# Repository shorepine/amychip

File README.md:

# AMY on a chip 

This repository collects "AMYchip" implementations, where we run the [AMY](https://github.com/shorepine/AMY) synthesizer on a full chip (doing nothing else), servicing requests over i2c (and future, SPI etc).

We have
 - [`esp32s3`](https://github.com/shorepine/amychip/tree/main/esp32s3)

And soon want to have
 - `rp2350`
 - `esp32p4`
 - `daisy`

## How to

Set your I2S and I2C pins at the top of the `amychip.c` in your chip's folder:

```c
#define I2S_BCLK 13 
#define I2S_LRCLK 12
#define I2S_DIN 11 // data going to the codec, eg DAC data
#define I2C_SLAVE_SCL 5  
#define I2C_SLAVE_SDA 4 
#define I2C_MASTER_SCL 17
#define I2C_MASTER_SDA 18
#define I2S_DOUT 16 // data coming from the codec, eg ADC  data
```

Set up your DAC / ADC codec. I'm using the [`WM8960`](https://www.sparkfun.com/products/21250) codec. Wire it up like:

```
Tulip or etc I2C/Mabee/Grove SCL -> I2C_SLAVE_SCL
Tulip or etc I2C/Mabee/Grove SDA -> I2C_SLAVE_SDA
Tulip or etc I2C/Mabee/Grove GND -> MCU GND
Tulip or etc I2C/Mabee/Grove 3.3V -> MCU 3V3
USB 5V -> MCU (we need 5V to power this codec)
WM8960 GND -> Audio in sleeve/GND
WM8960 LINPUT1 -> Audio in L
WM8960 RINPUT1 -> Audio in R
WM8960 HPL -> Audio out L
WM8960 OUT3 -> Audio out sleeve  *** NOTE: Audio-out "ground" is actually a special "mid-voltage" on OUT3
WM8960 HPR -> Audio out R
WM8960 BLCK -> I2S_BCLK
WM8960 DACLRC -> I2S_LRCLK (shared)
WM8960 DACDAT -> I2S_DIN
WM8960 ADCLRC -> I2S_LRCLK (shared)
WM8960 ADCDAT -> I2S_DOUT
WM8960 SCL -> I2C_MASTER_SCL
WM8960 SDA -> I2C_MASTER_SDA
WM8960 3V3 -> MCU 3V3
WM8960 VIN -> MCU 5V 
WM8960 GND -> MCU GND 
```

Compile / flash `amychip` using the instructions in the chip's folder.

Control the chip over I2C. In e.g. Tulip, that's as simple as 

```python
from machine import I2C
import amy
i2c = I2C(0, freq=400000)

amy.override_send= lambda x : i2c.writeto(0x58, bytes(x.encode('ascii')))
amy.send(reset=amy.RESET_TIMEBASE, time=tulip.ticks_ms()) # Restart the clock
```

You can get this on Tulip World:

```python
world.download('amychip.py')
execfile('amychip.py')
```

## Protocol

For now, over i2c, we just send AMY messages encoded as ASCII to `0x58`. Nothing gets returned. 

TODO:
 - ~~`memorypcm` / sample loading~~
 - stderr feedback over I2C
 - `sequencer.c`, sending interrupts to the "main" i2c host
 - SPI? UART?

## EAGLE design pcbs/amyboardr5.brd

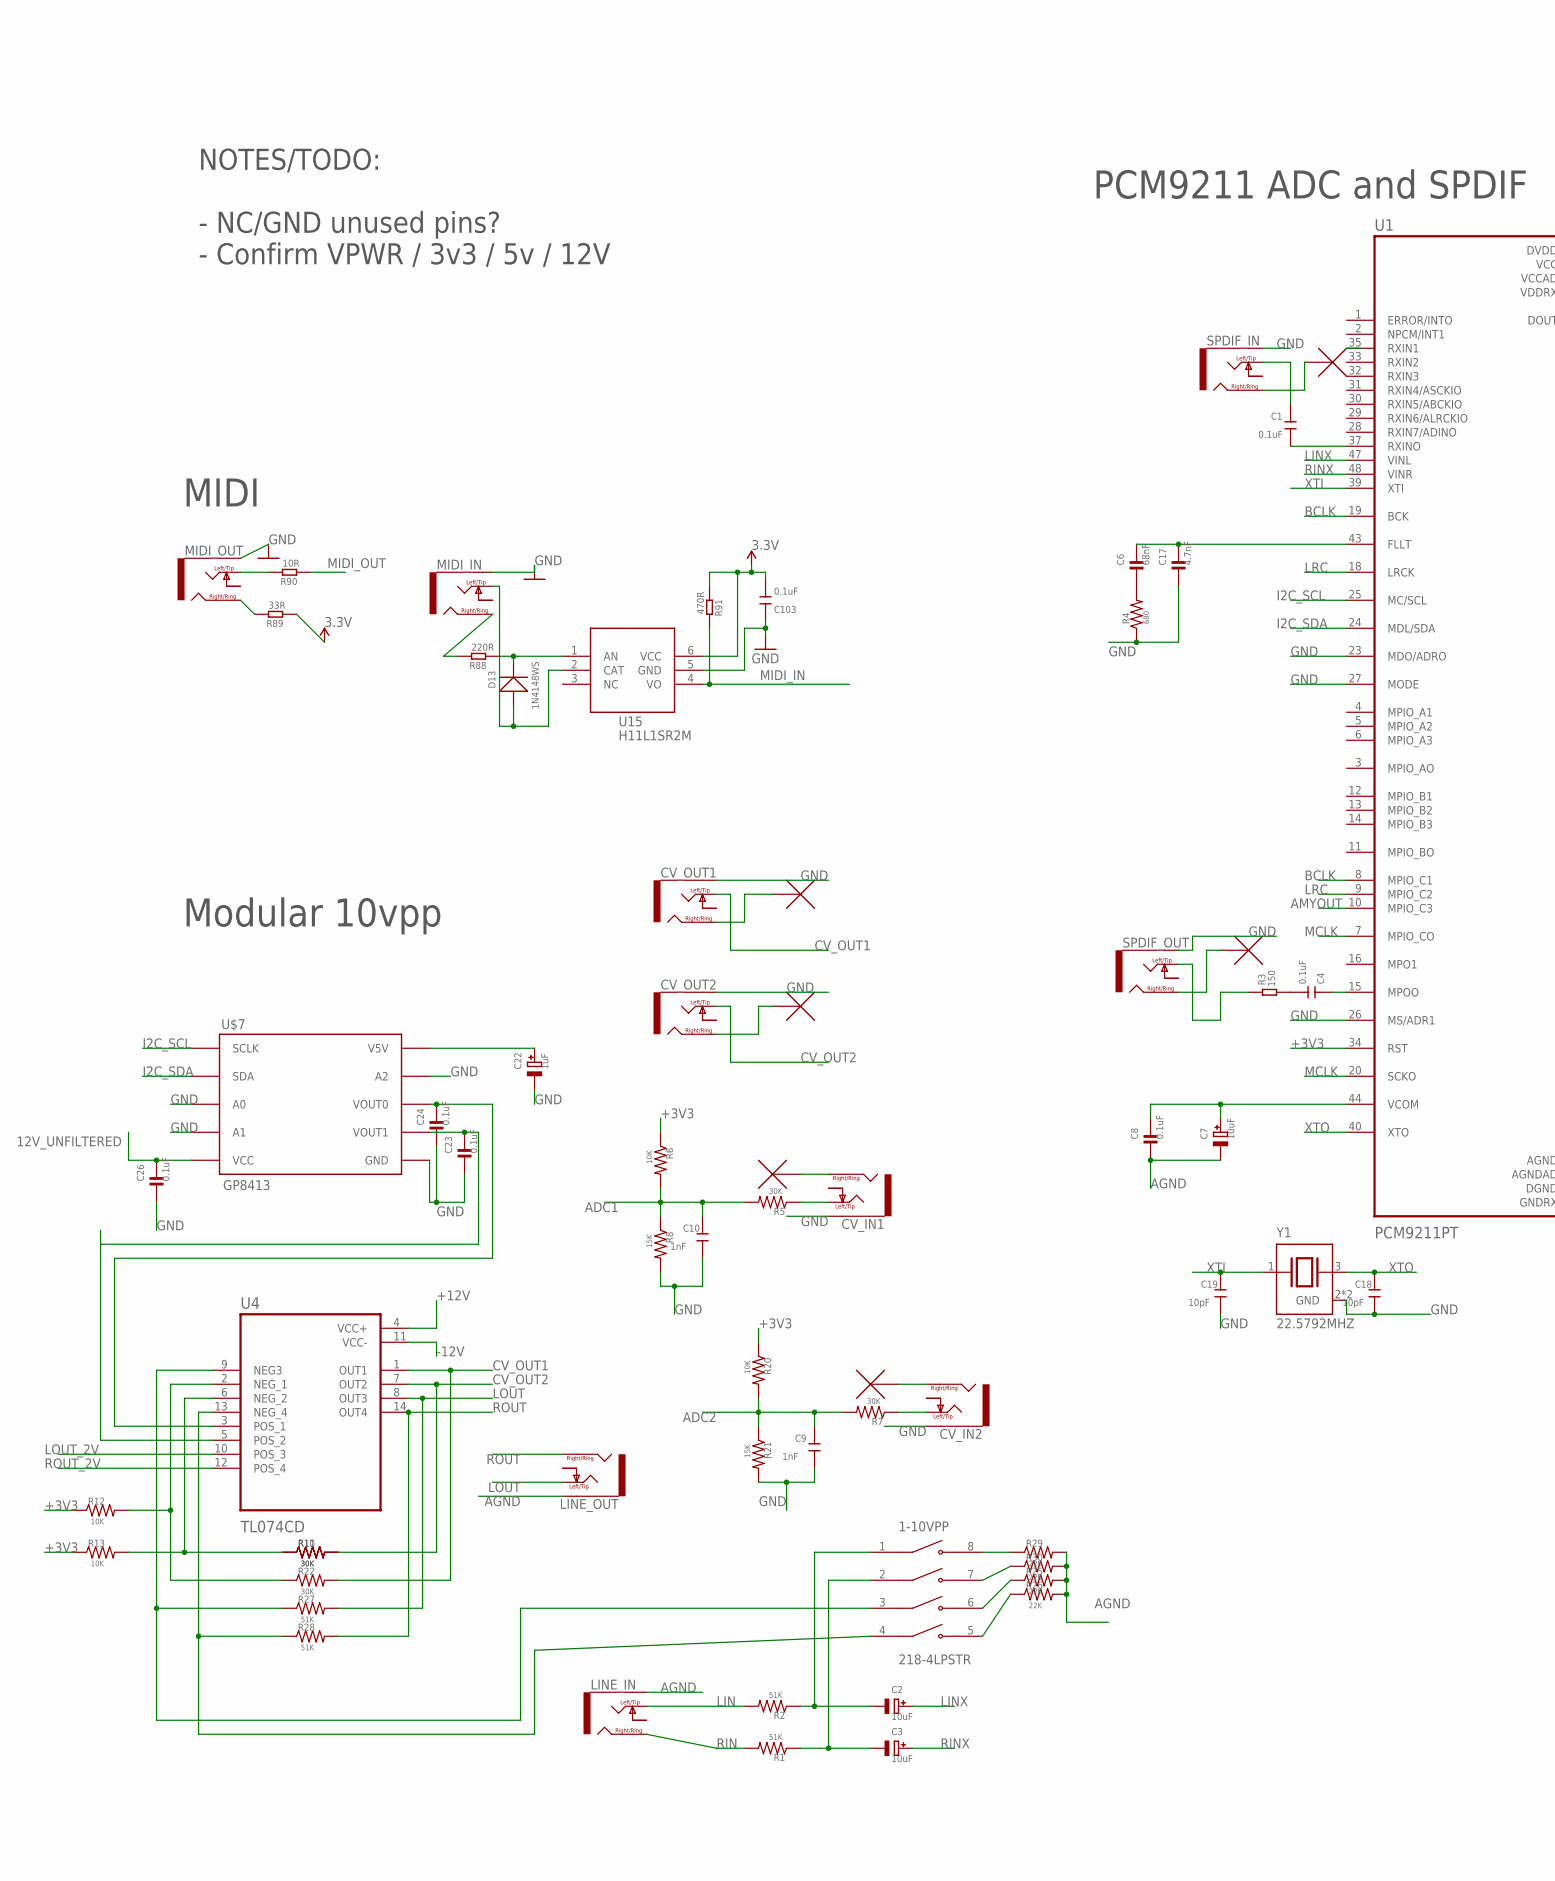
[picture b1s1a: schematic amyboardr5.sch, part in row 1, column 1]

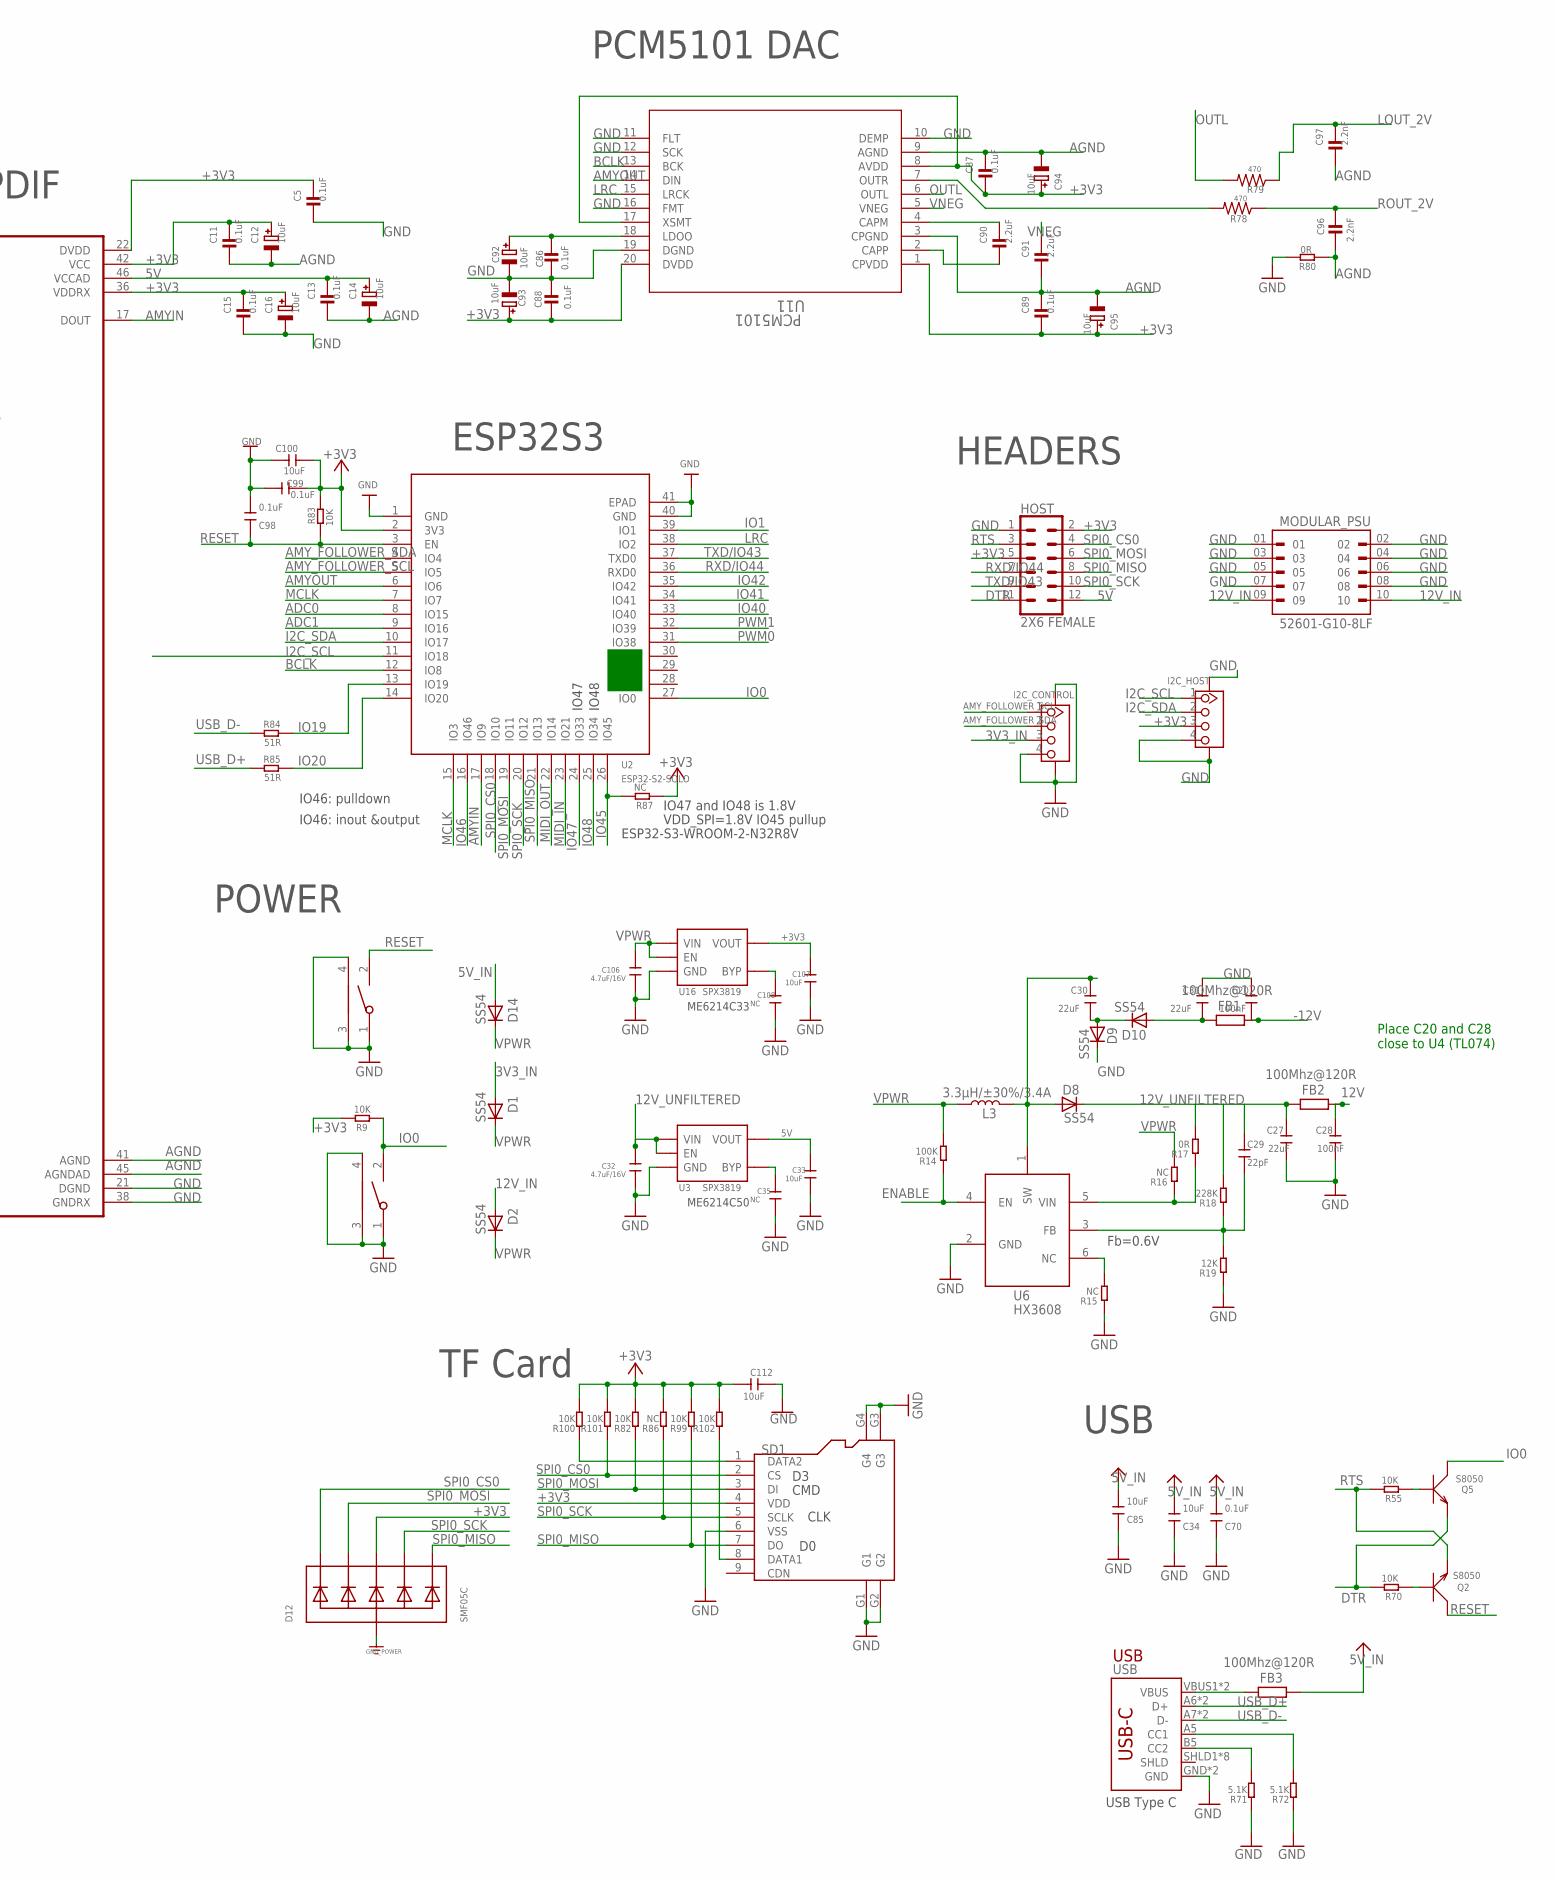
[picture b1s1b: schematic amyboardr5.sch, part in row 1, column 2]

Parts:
1-10VPP: 218-4LPSTR; SW_218-4LPSTR
BOOT: TS24CA; 2*4*3.5MM
C1, C4: 0.1uF; C0603
C2, C3, C7, C12, C14, C16, C92, C93, C94, C95: 10uF; PANASONIC_C
C5, C8, C11, C13, C15, C23, C24, C26, C86, C87, C88, C89: 0.1uF; 0805-NO@1
C6: 68nF; 0805-NO@1
C9, C10: 1nF; C0603
C17: 4.7nF; 0805-NO@1
C18, C19: 10pF; C0603
C20, C28: 100nF; C0603
C22: 1uF; PANASONIC_C
C27, C30, C31: 22uF; C0603
C29: 22pF; C0603
C32, C106: 4.7uF/16V; 0603
C33, C107: 10uF; 0603
C34, C85, C100, C112: 10uF; DISCRETE_C0603
C35, C108: NC; 0603
C70, C98, C99, C103: 0.1uF; DISCRETE_C0603
C90, C91: 2.2uF; 0805-NO@1
C96, C97: 2.2nF; 0805-NO@1
CV_IN1, CV_IN2: NV-PJ3410_STEREO; NV-PJ3410_SOCKET
CV_OUT1, CV_OUT2: NV-PJ3410_STEREO; NV-PJ3410_SOCKET
D1, D2, D8, D9, D10, D14: SS54; DO-214AC
D12: SMF05C; SOT363
D13: 1N4148WS; SOD323
FB1, FB2, FB3: 100Mhz@120R; R0805
HOST: 2X6 FEMALE; 2X6
I2C_CONTROL, I2C_HOST: GROVE-CONNECTOR-SMD'90D'; HW4-SMD-2.0-90D
L3: 3.3µH/±30%/3.4A; CR54
LINE_IN: NV-PJ3410_STEREO; NV-PJ3410_SOCKET
LINE_OUT: NV-PJ3410_STEREO; NV-PJ3410_SOCKET
MIDI_IN: NV-PJ3410_STEREO; NV-PJ3410_SOCKET
MIDI_OUT: NV-PJ3410_STEREO; NV-PJ3410_SOCKET
MODULAR_PSU: 52601-G10-8LF; AMPHENOL_52601-G10-8LF
PCM5101: U11; PW20_TEX
Q2, Q5: S8050; SOT23
R1, R2, R27, R28: 51K; R0805
R3: 150; DISCRETE_R0603
R4: 680; R0805
R5, R7, R10, R11, R22: 30K; R0805
R6, R12, R13, R20: 10K; R0805
R8, R21: 15K; R0805
R9, R55, R70, R83: 10K; R0603
R14: 100K; DISCRETE_R0603
R15, R16, R86: NC; DISCRETE_R0603
R17, R80: 0R; DISCRETE_R0603
R18: 228K; DISCRETE_R0603
R19: 12K; DISCRETE_R0603
R25, R26, R29, R30: 22K; R0805
R71, R72: 5.1K; DISCRETE_R0603
R78, R79: 470; R0805
R82, R99, R100, R101, R102: 10K; DISCRETE_R0603
R84, R85: 51R; R0603
R87: NC; R0603
R88: 220R; R0603
R89: 33R; R0603
R90: 10R; R0603
R91: 470R; R0603
RST: TS24CA; 2*4*3.5MM
SD1: HOLDER-MICROSD-9P; 9P-SMD-W/-RING
SPDIF_IN: NV-PJ3410_STEREO; NV-PJ3410_SOCKET
SPDIF_OUT: NV-PJ3410_STEREO; NV-PJ3410_SOCKET
U1: PCM9211PT; QFP50P900X900X160-48N
U2: ESP32­S2­SOLO; ESP32-­S2-­SOLO
U3, U16: SPX3819; SOT23-5
U4: TL074CD; SOIC127P600X175-14N
U6: HX3608; SOT-23-6
U15: H11L1SR2M; SOP-6-2.54MM
U$7: GP8413; SOIC-10
USB: USB_C5; USB-C-16P-5
Y1: 22.5792MHZ; XTAL_ABM10W-22.5792MHZ-8-K1Z-T3

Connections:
3.3V: C103.2, R89.1, R91.1, U15.6 (VCC)
3V3_IN: D1.A, I2C_CONTROL.3
5V: C13.1, C14.+, C33.1, HOST.12, U1.46 (VCCAD), U3.5 (VOUT)
5V_IN: C34.2, C70.2, C85.2, D14.A, FB3.2
12V: C28.1, FB2.2, R17.2
12V_IN: D2.A, MODULAR_PSU.09, MODULAR_PSU.10
12V_UNFILTERED: C26.1, C27.1, C32.1, D8.C, FB2.1, U3.1 (VIN), U3.3 (EN), U$7.5 (VCC)
+3V3: C5.1, C11.1, C12.+, C15.1, C16.+, C87.2, C88.2, C89.2, C93.+, C94.+, C95.+, C99.1, C100.1, C107.1, C112.2, D12.4 (C3), HOST.2, HOST.5, I2C_HOST.3, PCM5101.1 (CPVDD), PCM5101.8 (AVDD), PCM5101.17 (XSMT), PCM5101.20 (DVDD), R6.1, R9.2, R12.1, R13.1, R20.1, R82.2, R83.2, R86.2, R87.1, R99.2, R100.2, R101.2, R102.2, SD1.4 (VDD), U1.22 (DVDD), U1.34 (RST), U1.36 (VDDRX), U1.42 (VCC), U2.2 (3V3), U16.5 (VOUT)
+12V: U4.4 (VCC+)
-12V: C20.2, FB1.2, U4.11 (VCC-)
ADC0: U2.8 (IO15)
ADC1: C10.1, R5.2, R6.2, R8.1, U2.9 (IO16)
ADC2: C9.1, R7.2, R20.2, R21.1
AGND: C7.-, C8.2, C11.2, C12.-, C13.2, C14.-, C87.1, C89.1, C91.2, C94.-, C95.-, C96.2, C97.2, LINE_IN.GND (EARTH), LINE_OUT.GND (EARTH), PCM5101.3 (CPGND), PCM5101.9 (AGND), R25.2, R26.2, R29.2, R30.2, R80.1, U1.41 (AGND), U1.45 (AGNDAD)
AMYIN: U1.17 (DOUT), U2.17 (IO9)
AMYOUT: PCM5101.14 (DIN), U1.10 (MPIO_C3), U2.6 (IO6)
AMY_FOLLOWER_SCL: I2C_CONTROL.1, U2.5 (IO5)
AMY_FOLLOWER_SDA: I2C_CONTROL.2, U2.4 (IO4)
BCLK: PCM5101.13 (BCK), U1.8 (MPIO_C1), U1.19 (BCK), U2.12 (IO8)
CV_OUT1: CV_OUT1.LEFT/TIP (TIP), R22.2, U4.1 (OUT1)
CV_OUT2: CV_OUT2.LEFT/TIP (TIP), R10.2, R11.2, U4.7 (OUT2)
DTR: HOST.11, Q5.2 (E), R70.2
ENABLE: R14.1, U6.4 (EN)
GND: BOOT.1, BOOT.3, BOOT.4, C5.2, C9.2, C10.2, C15.2, C16.-, C17.2, C18.2, C19.2, C20.1, C22.-, C23.2, C24.2, C26.2, C27.2, C28.2, C31.1, C32.2, C33.2, C34.1, C35.2, C70.1, C85.1, C86.2, C88.1, C92.-, C93.-, C98.2, C99.2, C100.2, C103.1, C106.2, C107.2, C108.2, C112.1, CV_IN1.GND (EARTH), CV_IN2.GND (EARTH), CV_OUT1.GND (EARTH), CV_OUT2.GND (EARTH), D9.C, D12.2 (A), HOST.1, I2C_CONTROL.4, I2C_CONTROL.SS1, I2C_CONTROL.SS2, I2C_HOST.4, I2C_HOST.SS1, I2C_HOST.SS2, MIDI_IN.GND (EARTH), MIDI_OUT.GND (EARTH), MODULAR_PSU.01, MODULAR_PSU.02, MODULAR_PSU.03, MODULAR_PSU.04, MODULAR_PSU.05, MODULAR_PSU.06, MODULAR_PSU.07, MODULAR_PSU.08, PCM5101.10 (DEMP), PCM5101.11 (FLT), PCM5101.12 (SCK), PCM5101.16 (FMT), PCM5101.19 (DGND), R4.1, R8.2, R15.1, R19.1, R21.2, R71.1, R72.1, R80.2, RST.1, RST.3, RST.4, SD1.6 (VSS), SD1.G1, SD1.G2, SD1.G3, SD1.G4, SPDIF_IN.GND (EARTH), SPDIF_OUT.GND (EARTH), U1.21 (DGND), U1.23 (MDO/ADRO), U1.26 (MS/ADR1), U1.27 (MODE), U1.35 (RXIN1), U1.38 (GNDRX), U2.1 (GND), U2.40 (GND), U2.41 (EPAD), U3.2 (GND), U6.2 (GND), U15.5 (GND), U16.2 (GND), U$7.3 (A0), U$7.4 (A1), U$7.6 (GND), U$7.9 (A2), USB.GND, USB.GND2 (GND), Y1.2 (GND), Y1.4 (GND)
I2C_SCL: I2C_HOST.1, U1.25 (MC/SCL), U2.11 (IO18), U$7.1 (SCLK)
I2C_SDA: I2C_HOST.2, U1.24 (MDL/SDA), U2.10 (IO17), U$7.2 (SDA)
IO0: BOOT.2, Q5.3 (C), R9.1, U2.27 (IO0)
IO1: U2.39 (IO1)
IO19: R84.2, U2.13 (IO19)
IO20: R85.2, U2.14 (IO20)
IO40: U2.33 (IO40)
IO41: U2.34 (IO41)
IO42: U2.35 (IO42)
IO45: R87.2, U2.26 (IO45)
IO46: U2.16 (IO46)
IO47: U2.24 (IO33)
IO48: U2.25 (IO34)
LIN: LINE_IN.LEFT/TIP (TIP), R2.2
LINX: C2.+, U1.47 (VINL)
LOUT: LINE_OUT.LEFT/TIP (TIP), R27.2, U4.8 (OUT3)
LOUT_2V: C97.1, R79.1, U4.10 (POS_3)
LRC: PCM5101.15 (LRCK), U1.9 (MPIO_C2), U1.18 (LRCK), U2.38 (IO2)
MCLK: U1.7 (MPIO_CO), U1.20 (SCKO), U2.7 (IO7), U2.15 (IO3)
MIDI_IN: R91.2, U2.23 (IO21), U15.4 (VO)
MIDI_OUT: R90.1, U2.22 (IO14)
unnamed: C1.2, U1.37 (RXINO)
unnamed: C4.2, R3.2
unnamed: C4.1, U1.15 (MPOO)
unnamed: 1-10VPP.1, C2.-, R2.1
unnamed: 1-10VPP.2, C3.-, R1.1
unnamed: C7.+, C8.1, U1.44 (VCOM)
unnamed: C6.1, C17.1, U1.43 (FLLT)
unnamed: C6.2, R4.2
unnamed: CV_IN2.LEFT/TIP (TIP), R7.1
unnamed: C35.1, U3.4 (BYP)
unnamed: C31.2, D10.A, FB1.1
unnamed: C24.1, U4.3 (POS_1), U$7.8 (VOUT0)
unnamed: CV_IN1.LEFT/TIP (TIP), R5.1
unnamed: C23.1, U4.5 (POS_2), U$7.7 (VOUT1)
unnamed: C30.1, D8.A, L3.P$2 (2), U6.1 (SW)
unnamed: C22.+, U$7.10 (V5V)
unnamed: C29.2, R18.1, R19.2, U6.3 (FB)
unnamed: R15.2, U6.6 (NC)
unnamed: R16.1, R17.1, U6.5 (VIN)
unnamed: C30.2, D9.A, D10.C
unnamed: R10.1, R11.1, R13.2, U4.6 (NEG_2)
unnamed: R12.2, R22.1, U4.2 (NEG_1)
unnamed: Q2.1 (B), R70.1
unnamed: 1-10VPP.5, R26.1
unnamed: 1-10VPP.6, R25.1
unnamed: Q5.1 (B), R55.1
unnamed: R72.2, USB.A5 (CC1)
unnamed: R71.2, USB.B5 (CC2)
unnamed: 1-10VPP.8, R29.1
unnamed: 1-10VPP.7, R30.1
unnamed: FB3.1, USB.VBUS1 (VBUS), USB.VBUS2 (VBUS)
unnamed: 1-10VPP.3, R27.1, U4.9 (NEG3)
unnamed: 1-10VPP.4, R28.1, U4.13 (NEG_4)
unnamed: C86.1, C92.+, PCM5101.18 (LDOO)
unnamed: PCM5101.7 (OUTR), R78.2
unnamed: C90.1, PCM5101.4 (CAPM)
unnamed: C90.2, PCM5101.2 (CAPP)
unnamed: D13.+, MIDI_IN.LEFT/TIP (TIP), U15.2 (CAT)
unnamed: MIDI_IN.RIGHT/RING (RING), R88.2
unnamed: D13.-, R88.1, U15.1 (AN)
unnamed: MIDI_OUT.LEFT/TIP (TIP), R90.2
unnamed: MIDI_OUT.RIGHT/RING (RING), R89.2
unnamed: C108.1, U16.4 (BYP)
unnamed: R100.1, SD1.1 (DATA2)
unnamed: R102.1, SD1.8 (DATA1)
OUTL: PCM5101.6 (OUTL), R79.2
PWM0: U2.31 (IO38)
PWM1: U2.32 (IO39)
RESET: C98.1, Q2.3 (C), R83.1, RST.2, U2.3 (EN)
RIN: LINE_IN.RIGHT/RING (RING), R1.2
RINX: C3.+, U1.48 (VINR)
ROUT: LINE_OUT.RIGHT/RING (RING), R28.2, U4.14 (OUT4)
ROUT_2V: C96.1, R78.1, U4.12 (POS_4)
RTS: HOST.3, Q2.2 (E), R55.2
RXD/IO44: HOST.7, U2.36 (RXD0)
SPDIFIN_SIGNAL: C1.1, SPDIF_IN.LEFT/TIP (TIP)
SPDIFOUT_SIGNAL: R3.1, SPDIF_OUT.LEFT/TIP (TIP)
SPI0_CS0: D12.1 (C1), HOST.4, R101.1, SD1.2 (CS), U2.18 (IO10)
SPI0_MISO: D12.6 (C5), HOST.8, R99.1, SD1.7 (DO), U2.21 (IO13)
SPI0_MOSI: D12.3 (C2), HOST.6, R82.1, SD1.3 (DI), U2.19 (IO11)
SPI0_SCK: D12.5 (C4), HOST.10, R86.1, SD1.5 (SCLK), U2.20 (IO12)
TXD/IO43: HOST.9, U2.37 (TXD0)
USB_D+: R85.1, USB.A6 (D+), USB.B6 (D+)
USB_D-: R84.1, USB.A7 (D-), USB.B7 (D-)
VNEG: C91.1, PCM5101.5 (VNEG)
VPWR: C106.1, D1.C, D2.C, D14.C, L3.P$1 (1), R14.2, R16.2, U16.1 (VIN), U16.3 (EN)
XTI: C19.1, U1.39 (XTI), Y1.1
XTO: C18.1, U1.40 (XTO), Y1.3 (2)

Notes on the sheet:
USB
USB Type C
IO46: pulldown
IO46: inout &output
ESP32-S3-WROOM-2-N32R8V
IO47
IO48
IO47 and IO48 is 1.8V
VDD_SPI=1.8V IO45 pullup
POWER
ME6214C33
MIDI
PCM9211 ADC and SPDIF
ESP32S3
HEADERS
NOTES/TODO: - NC/GND unused pins? - Confirm VPWR / 3v3 / 5v / 12V
TF Card
CMD
CLK
Modular 10vpp
Fb=0.6V
ME6214C50
PCM5101 DAC
Place C20 and C28 close to U4 (TL074)

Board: 2 copper layers, 147 parts (11 on the bottom side), 102 nets, no tracks yet.

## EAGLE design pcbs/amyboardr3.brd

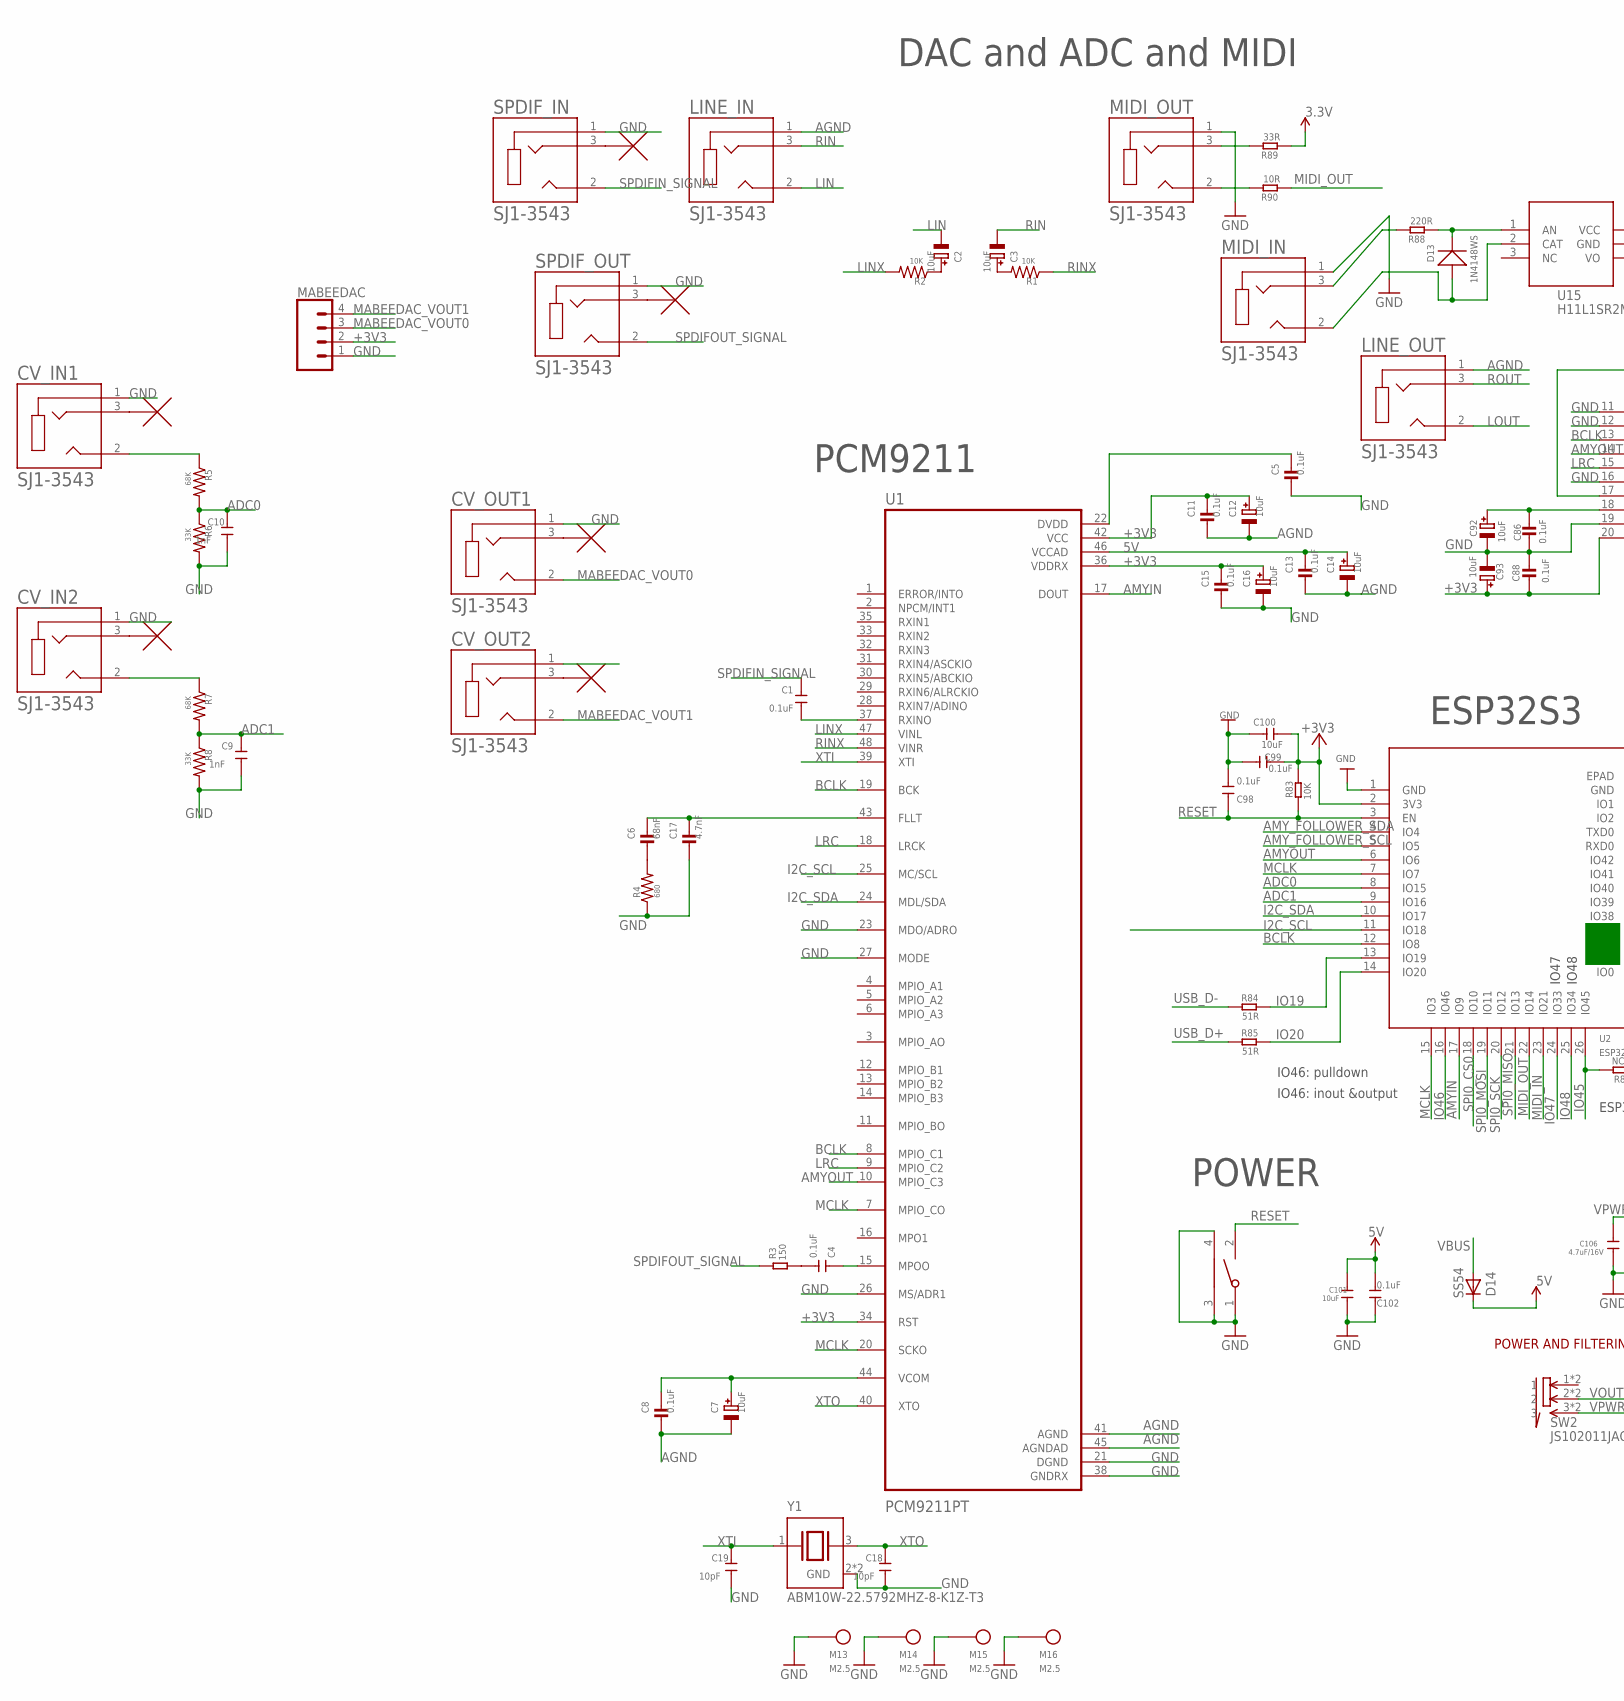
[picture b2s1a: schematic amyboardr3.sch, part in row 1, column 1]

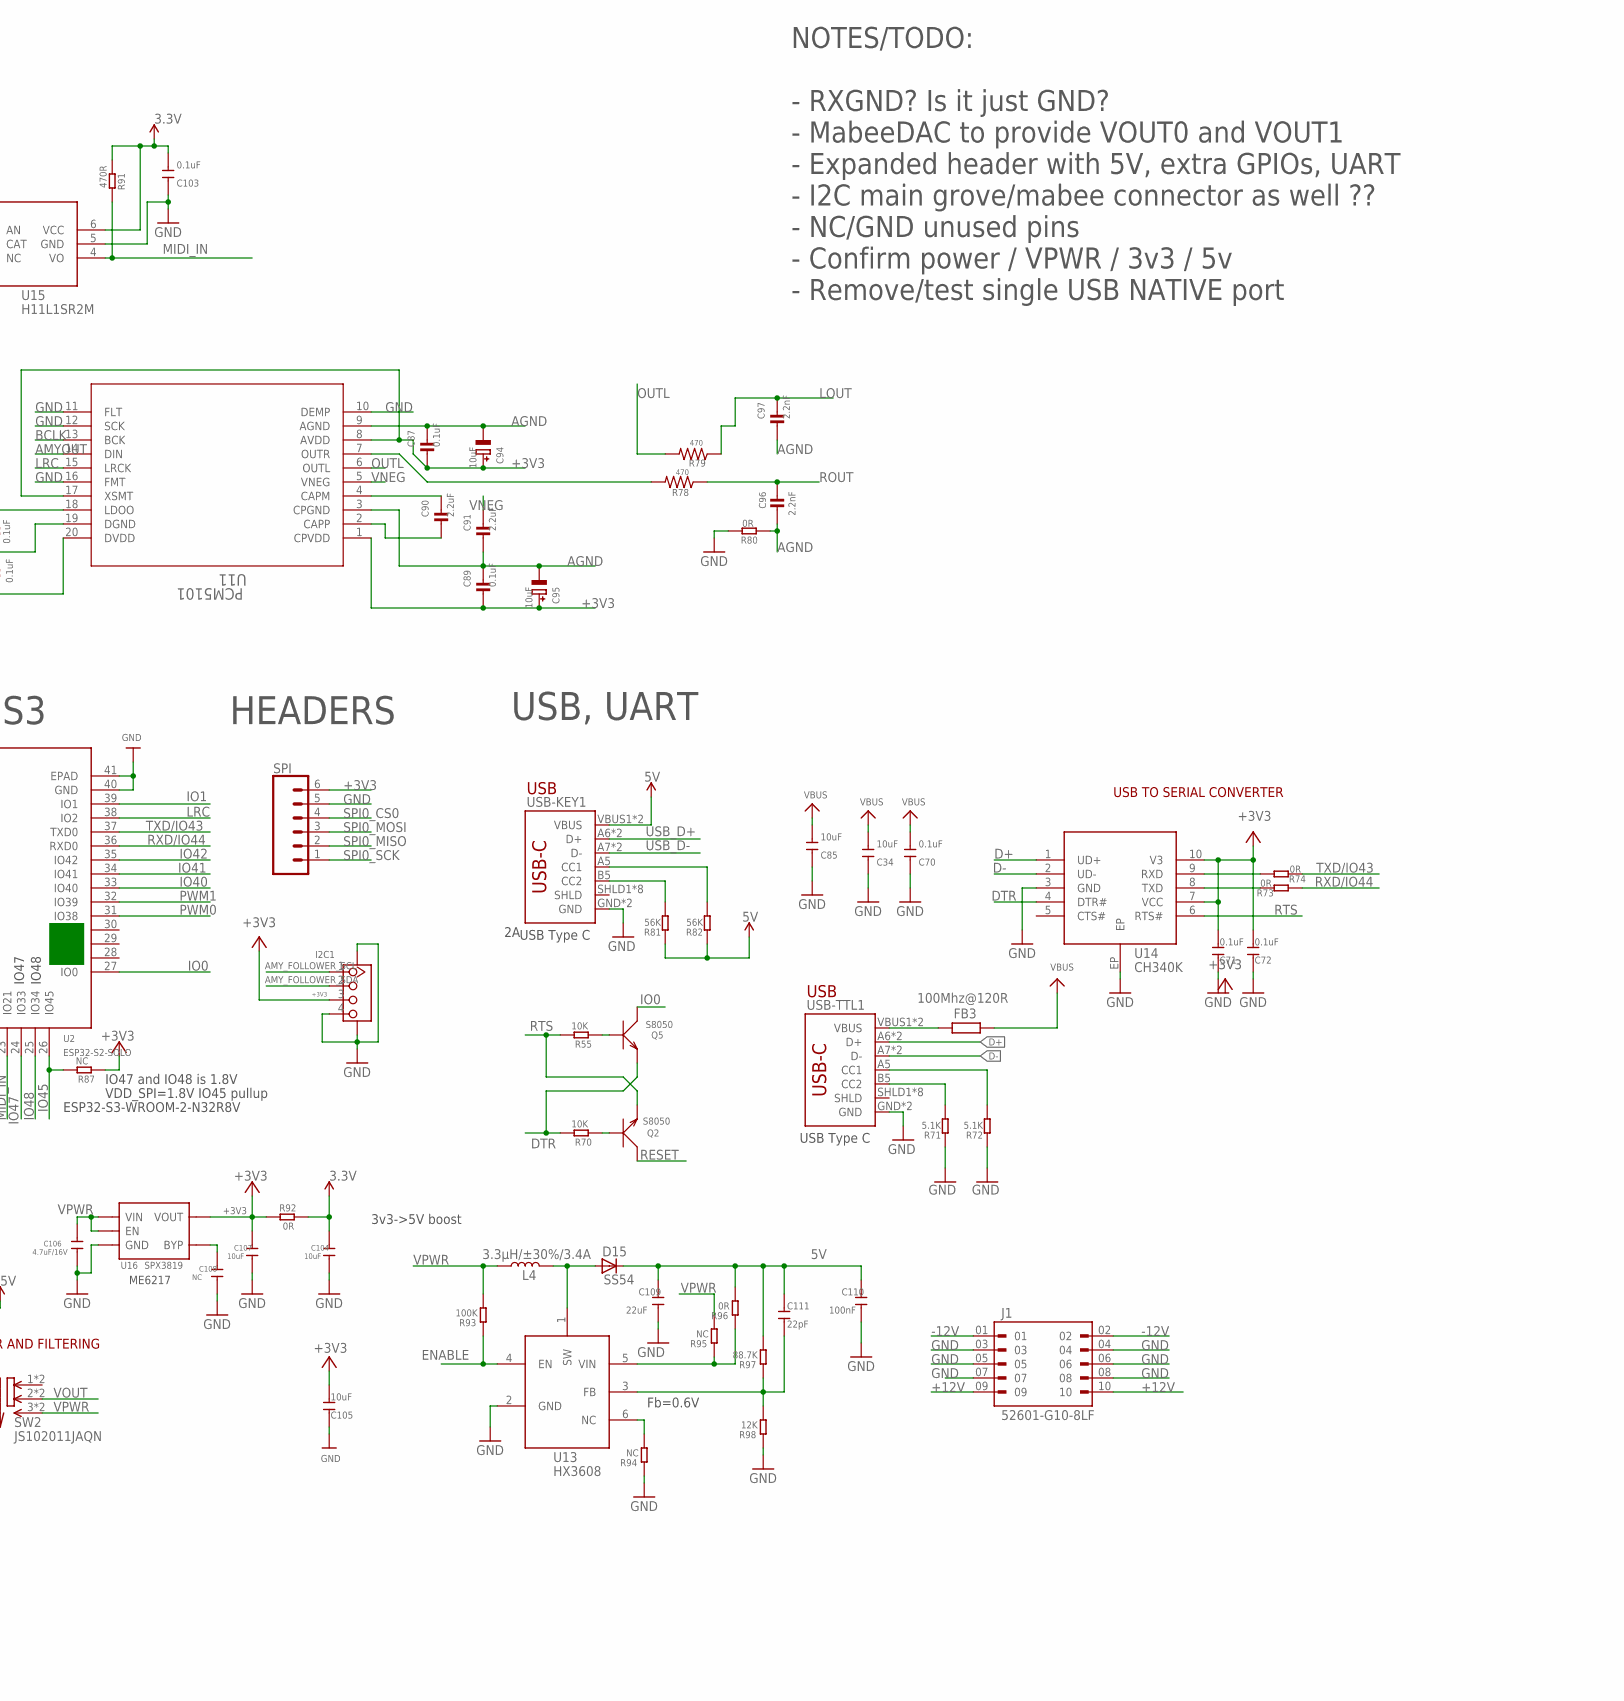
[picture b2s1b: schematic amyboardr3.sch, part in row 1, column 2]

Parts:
C1, C4: 0.1uF; C0603
C2, C3, C7, C12, C14, C16, C92, C93, C94, C95: 10uF; PANASONIC_C
C5, C8, C11, C13, C15, C86, C87, C88, C89: 0.1uF; 0805-NO@1
C6: 68nF; 0805-NO@1
C9, C10: 1nF; C0603
C17: 4.7nF; 0805-NO@1
C18, C19: 10pF; C0603
C34, C85, C100, C105: 10uF; DISCRETE_C0603
C70, C71, C72, C98, C99, C102, C103: 0.1uF; DISCRETE_C0603
C90, C91: 2.2uF; 0805-NO@1
C96, C97: 2.2nF; 0805-NO@1
C101, C104, C107: 10uF; 0603
C106: 4.7uF/16V; 0603
C108: NC; 0603
C109: 22uF; C0603
C110: 100nF; C0603
C111: 22pF; C0603
CV_IN1, CV_IN2: SJ1-3543; CUI_SJ1-3543
CV_OUT1, CV_OUT2: SJ1-3543; CUI_SJ1-3543
D13: 1N4148WS; SOD323
D14, D15: SS54; DO-214AC
FB3: 100Mhz@120R; R0805
I2C1: GROVE-CONNECTOR-SMD'90D'; HW4-SMD-2.0-90D
J1: 52601-G10-8LF; AMPHENOL_52601-G10-8LF
L4: 3.3µH/±30%/3.4A; CR54
LINE_IN: SJ1-3543; CUI_SJ1-3543
LINE_OUT: SJ1-3543; CUI_SJ1-3543
M13, M14, M15, M16: M2.5
MABEEDAC: CONN_04; 1X04
MIDI_IN: SJ1-3543; CUI_SJ1-3543
MIDI_OUT: SJ1-3543; CUI_SJ1-3543
PCM5101: U11; PW20_TEX
Q2, Q5: S8050; SOT23
R1, R2: 10K; R0805
R3: 150; DISCRETE_R0603
R4: 680; R0805
R5, R7: 68K; R0805
R6, R8: 33K; R0805
R55, R70, R83: 10K; R0603
R71, R72: 5.1K; DISCRETE_R0603
R73, R74, R92: 0R; R0603
R78, R79: 470; R0805
R80, R96: 0R; DISCRETE_R0603
R81, R82: 56K; DISCRETE_R0603
R84, R85: 51R; R0603
R87: NC; R0603
R88: 220R; R0603
R89: 33R; R0603
R90: 10R; R0603
R91: 470R; R0603
R93: 100K; DISCRETE_R0603
R94, R95: NC; DISCRETE_R0603
R97: 88.7K; DISCRETE_R0603
R98: 12K; DISCRETE_R0603
RST1: TS24CA; 2*4*3.5MM
SPDIF_IN: SJ1-3543; CUI_SJ1-3543
SPDIF_OUT: SJ1-3543; CUI_SJ1-3543
SPI: CONN_06SILK_FEMALE_PTH; 1X06
SW2: JS102011JAQN; SMD-6-2.5MM
U1: PCM9211PT; QFP50P900X900X160-48N
U2: ESP32­S2­SOLO; ESP32-­S2-­SOLO
U13: HX3608; SOT-23-6
U14: CH340K; ESOP-10-EP-150MIL
U15: H11L1SR2M; SOP-6-2.54MM
U16: SPX3819; SOT23-5
USB-KEY1: USB_C5; USB-C-16P-5
USB-TTL1: USB_C5; USB-C-16P-5
Y1: ABM10W-22.5792MHZ-8-K1Z-T3; XTAL_ABM10W-22.5792MHZ-8-K1Z-T3

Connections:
3.3V: C103.2, C104.1, R89.1, R91.1, R92.2, U15.6 (VCC)
5V: C13.1, C14.+, C101.1, C102.2, C109.1, C110.1, C111.1, D14.C, D15.C, R81.1, R82.1, R96.2, R97.2, U1.46 (VCCAD), USB-KEY1.VBUS1 (VBUS), USB-KEY1.VBUS2 (VBUS)
+3V3: C5.1, C11.1, C12.+, C15.1, C16.+, C71.2, C72.2, C87.2, C88.2, C89.2, C93.+, C94.+, C95.+, C99.1, C100.1, C105.2, C107.1, I2C1.3, MABEEDAC.2, PCM5101.1 (CPVDD), PCM5101.8 (AVDD), PCM5101.17 (XSMT), PCM5101.20 (DVDD), R83.2, R87.1, R92.1, SPI.6, U1.22 (DVDD), U1.34 (RST), U1.36 (VDDRX), U1.42 (VCC), U2.2 (3V3), U14.7 (VCC), U14.10 (V3), U16.5 (VOUT)
+12V: J1.09, J1.10
-12V: J1.01, J1.02
ADC0: C10.1, R5.2, R6.1, U2.8 (IO15)
ADC1: C9.1, R7.2, R8.1, U2.9 (IO16)
AGND: C7.-, C8.2, C11.2, C12.-, C13.2, C14.-, C87.1, C89.1, C91.2, C94.-, C95.-, C96.2, C97.2, LINE_IN.1, LINE_OUT.1, PCM5101.3 (CPGND), PCM5101.9 (AGND), R80.1, U1.41 (AGND), U1.45 (AGNDAD)
AMYIN: U1.17 (DOUT), U2.17 (IO9)
AMYOUT: PCM5101.14 (DIN), U1.10 (MPIO_C3), U2.6 (IO6)
AMY_FOLLOWER_SCL: I2C1.1, U2.5 (IO5)
AMY_FOLLOWER_SDA: I2C1.2, U2.4 (IO4)
BCLK: PCM5101.13 (BCK), U1.8 (MPIO_C1), U1.19 (BCK), U2.12 (IO8)
D+: U14.1 (UD+), USB-TTL1.A6 (D+), USB-TTL1.B6 (D+)
D-: U14.2 (UD-), USB-TTL1.A7 (D-), USB-TTL1.B7 (D-)
DTR: Q5.2 (E), R70.2, U14.4 (DTR#)
ENABLE: R93.1, U13.4 (EN)
GND: C5.2, C9.2, C10.2, C15.2, C16.-, C17.2, C18.2, C19.2, C34.1, C70.1, C71.1, C72.1, C85.1, C86.2, C88.1, C92.-, C93.-, C98.2, C99.2, C100.2, C101.2, C102.1, C103.1, C104.2, C105.1, C106.2, C107.2, C108.2, C109.2, C110.2, CV_IN1.1, CV_IN2.1, CV_OUT1.1, I2C1.4, I2C1.SS1, I2C1.SS2, J1.03, J1.04, J1.05, J1.06, J1.07, J1.08, M13.1, M14.1, M15.1, M16.1, MABEEDAC.1, MIDI_IN.1, MIDI_OUT.1, PCM5101.10 (DEMP), PCM5101.11 (FLT), PCM5101.12 (SCK), PCM5101.16 (FMT), PCM5101.19 (DGND), R4.1, R6.2, R8.2, R71.1, R72.1, R80.2, R94.1, R98.1, RST1.1, RST1.3, RST1.4, SPDIF_IN.1, SPDIF_OUT.1, SPI.5, U1.21 (DGND), U1.23 (MDO/ADRO), U1.26 (MS/ADR1), U1.27 (MODE), U1.38 (GNDRX), U2.1 (GND), U2.40 (GND), U2.41 (EPAD), U13.2 (GND), U14.3 (GND), U14.EP, U15.5 (GND), U16.2 (GND), USB-KEY1.GND, USB-KEY1.GND2 (GND), USB-TTL1.GND, USB-TTL1.GND2 (GND), Y1.2 (GND), Y1.4 (GND)
I2C_SCL: U1.25 (MC/SCL), U2.11 (IO18)
I2C_SDA: U1.24 (MDL/SDA), U2.10 (IO17)
IO0: Q5.3 (C), U2.27 (IO0)
IO1: U2.39 (IO1)
IO19: R84.2, U2.13 (IO19)
IO20: R85.2, U2.14 (IO20)
IO40: U2.33 (IO40)
IO41: U2.34 (IO41)
IO42: U2.35 (IO42)
IO45: R87.2, U2.26 (IO45)
IO46: U2.16 (IO46)
IO47: U2.24 (IO33)
IO48: U2.25 (IO34)
LIN: C2.-, LINE_IN.2
LINX: R2.2, U1.47 (VINL)
LOUT: C97.1, LINE_OUT.2, R79.1
LRC: PCM5101.15 (LRCK), U1.9 (MPIO_C2), U1.18 (LRCK), U2.38 (IO2)
MABEEDAC_VOUT0: CV_OUT1.2, MABEEDAC.3
MABEEDAC_VOUT1: CV_OUT2.2, MABEEDAC.4
MCLK: U1.7 (MPIO_CO), U1.20 (SCKO), U2.7 (IO7), U2.15 (IO3)
MIDI_IN: R91.2, U2.23 (IO21), U15.4 (VO)
MIDI_OUT: R90.1, U2.22 (IO14)
unnamed: C1.2, U1.37 (RXINO)
unnamed: C4.2, R3.2
unnamed: C4.1, U1.15 (MPOO)
unnamed: C2.+, R2.1
unnamed: C3.+, R1.2
unnamed: C7.+, C8.1, U1.44 (VCOM)
unnamed: C6.1, C17.1, U1.43 (FLLT)
unnamed: C6.2, R4.2
unnamed: CV_IN1.2, R5.1
unnamed: CV_IN2.2, R7.1
unnamed: Q2.1 (B), R70.1
unnamed: Q5.1 (B), R55.1
unnamed: R72.2, USB-TTL1.A5 (CC1)
unnamed: R71.2, USB-TTL1.B5 (CC2)
unnamed: R74.2, U14.9 (RXD)
unnamed: R73.2, U14.8 (TXD)
unnamed: FB3.1, USB-TTL1.VBUS1 (VBUS), USB-TTL1.VBUS2 (VBUS)
unnamed: C86.1, C92.+, PCM5101.18 (LDOO)
unnamed: PCM5101.7 (OUTR), R78.2
unnamed: C90.1, PCM5101.4 (CAPM)
unnamed: C90.2, PCM5101.2 (CAPP)
unnamed: R82.2, USB-KEY1.A5 (CC1)
unnamed: R81.2, USB-KEY1.B5 (CC2)
unnamed: D13.+, MIDI_IN.2, U15.2 (CAT)
unnamed: MIDI_IN.3, R88.2
unnamed: D13.-, R88.1, U15.1 (AN)
unnamed: MIDI_OUT.2, R90.2
unnamed: MIDI_OUT.3, R89.2
unnamed: C108.1, U16.4 (BYP)
unnamed: D15.A, L4.P$2 (2), U13.1 (SW)
unnamed: C111.2, R97.1, R98.2, U13.3 (FB)
unnamed: R94.2, U13.6 (NC)
unnamed: R95.1, R96.1, U13.5 (VIN)
OUTL: PCM5101.6 (OUTL), R79.2
PWM0: U2.31 (IO38)
PWM1: U2.32 (IO39)
RESET: C98.1, Q2.3 (C), R83.1, RST1.2, U2.3 (EN)
RIN: C3.-, LINE_IN.3
RINX: R1.1, U1.48 (VINR)
ROUT: C96.1, LINE_OUT.3, R78.1
RTS: Q2.2 (E), R55.2, U14.6 (RTS#)
RXD/IO44: R73.1, U2.36 (RXD0)
SPDIFIN_SIGNAL: C1.1, SPDIF_IN.2
SPDIFOUT_SIGNAL: R3.1, SPDIF_OUT.2
SPI0_CS0: SPI.4, U2.18 (IO10)
SPI0_MISO: SPI.2, U2.21 (IO13)
SPI0_MOSI: SPI.3, U2.19 (IO11)
SPI0_SCK: SPI.1, U2.20 (IO12)
TXD/IO43: R74.1, U2.37 (TXD0)
USB_D+: R85.1, USB-KEY1.A6 (D+), USB-KEY1.B6 (D+)
USB_D-: R84.1, USB-KEY1.A7 (D-), USB-KEY1.B7 (D-)
VBUS: C34.2, C70.2, C85.2, D14.A, FB3.2
VNEG: C91.1, PCM5101.5 (VNEG)
VOUT: SW2.2, SW2.2@1 (2)
VPWR: C106.1, L4.P$1 (1), R93.2, R95.2, SW2.3, SW2.3@1 (3), U16.1 (VIN), U16.3 (EN)
XTI: C19.1, U1.39 (XTI), Y1.1
XTO: C18.1, U1.40 (XTO), Y1.3 (2)

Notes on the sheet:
USB
USB TO SERIAL CONVERTER
USB, UART
USB Type C
IO46: pulldown
IO46: inout &output
ESP32-S3-WROOM-2-N32R8V
IO47
IO48
IO47 and IO48 is 1.8V
VDD_SPI=1.8V IO45 pullup
POWER AND FILTERING
POWER
ME6217
Fb=0.6V
3v3->5V boost
DAC and ADC and MIDI
PCM9211
ESP32S3
HEADERS
NOTES/TODO: - RXGND? Is it just GND? - MabeeDAC to provide VOUT0 and VOUT1 - Expanded header with 5V, extra GPIOs, UART - I2C main grove/mabee connector as well ?? - NC/GND unused pins - Confirm power / VPWR / 3v3 / 5v - Remove/test single USB NATIVE port

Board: 2 copper layers, 121 parts (5 on the bottom side), 88 nets, no tracks yet.

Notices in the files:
parts and their libraries:
microbuilder: This work is placed in the public domain, and may be freely used for commercial and non-commercial work with the following conditions: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
COPYRIGHT: Copyright (C) 2022 Ultra Librarian. All rights reserved.
